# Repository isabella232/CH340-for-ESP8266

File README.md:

# USB-Serial converter for ESP8266 auto program

DTR, RTS を利用して ESP8266(ESP-WROOM-02) のリセットを制御。Arduino での書き込みを自動化する。

はんだごてでハンダづけでき、わりかしコンパクトなフットプリント。

3.3V 専用。

`J1` ピンはショットキーバリアダイオードを通る分、5V から電圧降下(0.3～0.4V)します。

# ボード

# 回路図

# 部品表

| 部品番号       | 値                 | 部品名                                      | 入手先   | 備考                                                             |
| -------------- | ------------------ | ------------------------------------------- | -------- | ---------------------------------------------------------------- |
| D1             | 30V1A              | ショットキーバリアダイオード RSX101VAM-30TR | 秋月電子 | [I-05951](http://akizukidenshi.com/catalog/g/gI-05951/)          |
| PTC1           | 0.75A6V(2012)      | リセッタブルフューズ PICOSMDC075S-2         | eBay     | https://www.ebay.com/itm/263051781459                            |
| X1             |                    | USBコネクタ(A/オス) UAM-21BK                | aitendo  | http://www.aitendo.com/product/16665                             |
| C1/C2          | 22pF50V(1608)      | 積セラコンデンサ                            | aitendo  | http://www.aitendo.com/product/6989                              |
| Q4             | 12MHz              | クリスタル（2x6）                           | aitendo  | http://www.aitendo.com/product/5028                              |
| C3             | 0.1uF50V(1608)     | 積セラコンデンサ GRM188F11H104ZA01          | 秋月電子 | [P-13374](http://akizukidenshi.com/catalog/g/gP-13374/)          |
| C4/C5          | 10uF25V(2012)      | 積セラコンデンサ GRM21BB31E106KA            | 秋月電子 | [P-13388](http://akizukidenshi.com/catalog/g/gP-13388/)          |
| IC1            |                    | USB-シリアルコンバータ CH340G               | aitendo  | http://www.aitendo.com/product/11576                             |
| C6             | 22uF25V(1608)            | 積セラコンデンサ GRM21BR61E226ME44          | 秋月電子 | [P-08240](http://akizukidenshi.com/catalog/g/gP-08240/) 47uF がいいかも [mouser](https://www.mouser.jp/Passive-Components/Capacitors/Ceramic-Capacitors/MLCCs-Multilayer-Ceramic-Capacitors/Multilayer-Ceramic-Capacitors-MLCC-SMD-SMT/_/N-bkrdv?P=1z0wrk9Z1yx4avtZ1yzmou5)        |
| IC2            | 3.3V               | レギュレータ AMS1117-3.3 や AZ1086H-3.3     | 秋月電子 | [I-02502](http://akizukidenshi.com/catalog/g/gI-02502/)          |
| R1/R2/R3/R4/R5 | 470Ω(1608)         | チップ抵抗                                  | 千石電商 | https://www.sengoku.co.jp/mod/sgk_cart/detail.php?code=EEHD-57GC |
| LED1           | VF=1.9～2.1V(1608) | オレンジ色チップLED                         | 秋月電子 | [I-06416](http://akizukidenshi.com/catalog/g/gI-06416/)          |
| LED2           | VF=1.9～2.1V(1608) | 黄緑色チップLED                             | 秋月電子 | [I-03980](http://akizukidenshi.com/catalog/g/gI-03980)           |
| LED3           | VF=1.9～2.1V(1608) | 赤色チップLED                               | 秋月電子 | [I-03978](http://akizukidenshi.com/catalog/g/gI-03978)           |
| CON1           | ZHコネクタ6ピン    | S6B-ZR                                      | 秋月電子 | [C-14164](http://akizukidenshi.com/catalog/g/gC-14164/) ワイヤ直付けでもよいと思います         |
| Q1/Q2          |                    | LMUN2233LT1G                                | eBay     | https://www.ebay.com/itm/262770111020                            |
|                | E40X18.5X9.6B      | USBプラケース                               | aitendo  | http://www.aitendo.com/product/16537                             |

# できあがり

## 表面

## 裏面

## ケースに入れて接続した状態

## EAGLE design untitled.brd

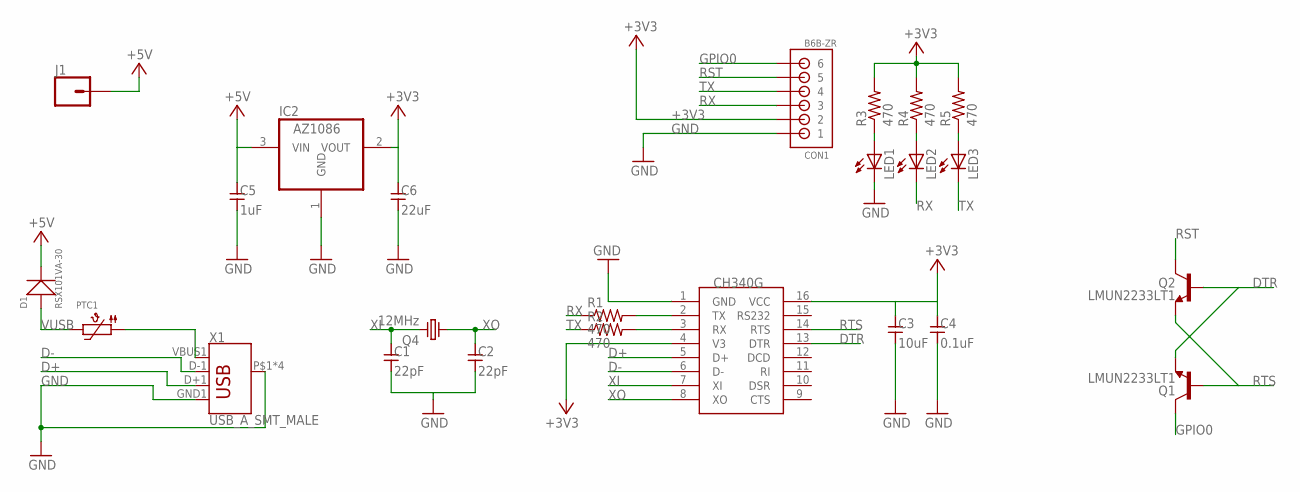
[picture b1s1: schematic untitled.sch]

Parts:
C1, C2: 22pF; SMD1608
C3: 10uF; SMD1608
C4: 0.1uF; SMD1608
C5: 1uF; SMD1608
C6: 22uF; SMD1608
CON1: B6B-ZR
D1: RSX101VA-30; TUMD2
IC2: AZ1086; SOT223
J1: CONN_01PTH_NO_SILK_YES_STOP; 1X01_NO_SILK
LED1, LED2, LED3: LEDCHIPLED_0603; CHIPLED_0603
PTC1: PTC0805; 0805
Q1, Q2: LMUN2233LT1; SOT23-3
Q4: 12MHz; TC26H
R1, R2, R3, R4, R5: 470; R0603
U$1: CH340G; SOIC16
X1: USB_A_SMT_MALE; USB-A-SMT-MALE

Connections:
+3V3: C3.1, C4.1, C6.1, CON1.2, IC2.2 (VOUT), R3.2, R4.2, R5.2, U$1.4 (V3), U$1.16 (VCC)
+5V: C5.1, D1.-, IC2.3 (VIN), J1.1
D+: U$1.5 (D+), X1.D+1 (D+)
D-: U$1.6 (D-), X1.D-1 (D-)
DTR: Q1.3 (E), Q2.1 (B), U$1.13 (DTR)
GND: C1.2, C2.2, C3.2, C4.2, C5.2, C6.2, CON1.1, IC2.1 (GND), LED1.C, U$1.1 (GND), X1.GND1 (GND), X1.P$1 (SHIELD), X1.P$2 (SHIELD), X1.P$3 (SHIELD), X1.P$4 (SHIELD)
GPIO0: CON1.6, Q1.2 (C)
unnamed: PTC1.1, X1.VBUS1 (VBUS)
unnamed: LED1.A, R3.1
unnamed: LED2.A, R4.1
unnamed: LED3.A, R5.1
RST: CON1.5, Q2.2 (C)
RTS: Q1.1 (B), Q2.3 (E), U$1.14 (RTS)
RX: CON1.3, LED2.C, R1.1
RXD: R2.2, U$1.3 (RX)
TX: CON1.4, LED3.C, R2.1
TXD: R1.2, U$1.2 (TX)
VUSB: D1.+, PTC1.2
XI: C1.1, Q4.2, U$1.7 (XI)
XO: C2.1, Q4.1, U$1.8 (XO)

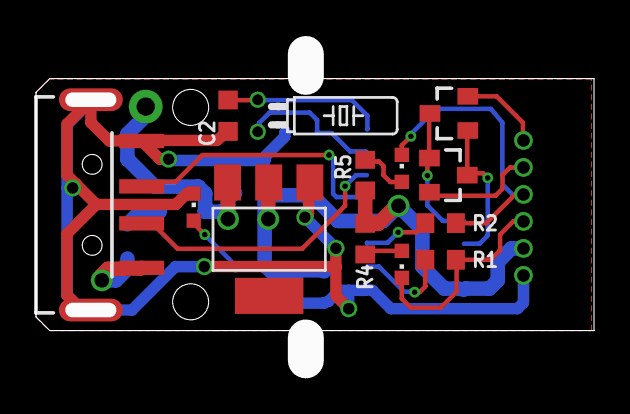
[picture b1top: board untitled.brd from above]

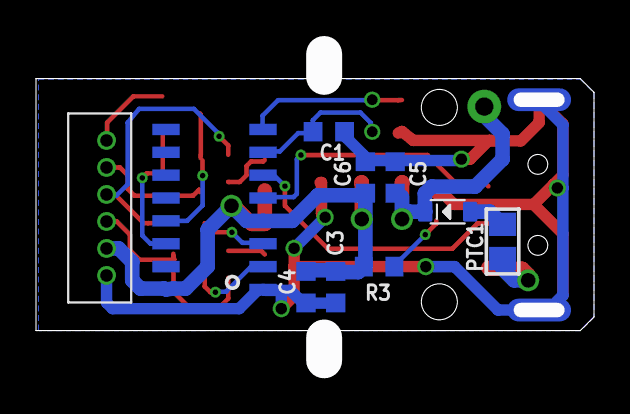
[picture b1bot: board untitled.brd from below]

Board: 2 copper layers, 29.0 x 17.0 mm, 24 parts (10 on the bottom side), 20 nets.

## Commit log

2017-10-19 CH340
2017-11-22 CH340G rev.2
2018-03-02 Added.
2019-10-16 Added .gitignore
2019-10-16 Deleted gerber file.
2019-10-16 Renamed eagle file name.
2019-11-19 Added README and images.
2019-11-20 CON1 はワイヤ直付けでもよいと思います
2019-11-20 C6 は 47uF のほうがレギュレータ安定するかも
2022-08-01 [ImgBot] Optimize images
    *Total -- 475.03kb -> 389.35kb (18.04%)
    /doc/ch340-brd.png -- 127.02kb -> 67.44kb (46.91%)
    /doc/ch340-sch.png -- 25.05kb -> 14.79kb (40.97%)
    /doc/done.jpg -- 80.99kb -> 75.25kb (7.08%)
    /doc/front.jpg -- 113.80kb -> 108.46kb (4.7%)
    /doc/back.jpg -- 128.17kb -> 123.42kb (3.71%)

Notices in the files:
parts and their libraries:
microbuilder: This work is placed in the public domain, and may be freely used for commercial and non-commercial work with the following conditions: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
SparkFun-Connectors: Licensing: Creative Commons ShareAlike 4.0 International - https://creativecommons.org/licenses/by-sa/4.0
